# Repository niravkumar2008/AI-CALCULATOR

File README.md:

# AI Calculator

> **Update 2026-10-11:** this README describes the e-paper prototype firmware and simulators in this branch.
> Current state: the product is branded **Proofline**; the **v15 colour-LCD board** is ordered (5 samples, then
> bulk; v14 was never ordered) and its firmware lives on branch `claude/v15-mode4-menu`, where **MODE 4 opens
> Apps** (AI Solve, Type it, History, Notes, Geography, Periodic Table, Settings incl. Link calculator) and exam
> mode turns all apps off. The website, subscription server and store are in `web/` (start with
> [web/SITE_README.md](web/SITE_README.md) and [docs/web/GUIDE.md](docs/web/GUIDE.md)); nothing is deployed.
> The firmware still talks to the older Python server/proxy; connecting it to the new server is the open
> "stage 2" of [docs/web/PLAN.md](docs/web/PLAN.md). (The "Stage 2" and "Stage 4" headings below are the
> firmware's own older stage numbers, not the web plan's.)

## Stage 4: the full calculator

The device now works like a Casio fx-300ES PLUS in COMP mode, with the AI photo solver as mode 4 in the MODE menu. The same C++ code runs in three places:

| Where | How |
| --- | --- |
| **Browser** | `AI_Calc_Simulator.html` (next to the exe; same as `sim/web/simulator.html`): double-click to open in Chrome or Edge. Clickable keypad, test bench (demo replies, hotspot/key switches, clock fast-forward, USB unlock). For real scans, pick Photo or Typed problem and paste your API key: it then sends exactly what the ESP32 sends (upright, grayscale, max 1600 px JPEG, same request, model, streaming and error handling). Direct API calls only work in this local file; the Claude artifact page blocks them. |
| **Windows** | `AI_Calc_Simulator.exe`: type on the keyboard (key list at the bottom of the window). **F6 scans a photo** (needs `api_key.txt` next to the exe). |
| **Tester** | `firmware/`: see [firmware/README.md](firmware/README.md). |

What the calculator does:

- **COMP maths:** + − × ÷, exact fractions (1÷3 = 1⌟3, S⇔D for decimal), powers, roots, x², x³, x⁻¹, x!, nPr, nCr, log (with base), ln, eˣ, 10ˣ, sin/cos/tan and inverses, hyp menu, Abs, %, π, e, Ran#, Rnd, ENG. Casio priorities: implicit × binds tighter than ÷ (1÷2π = 1÷(2π)), (−)2² = −4, brackets close themselves at the end. 10 significant digits, Norm1/Norm2.
- **Editing:** cursor with ◀ ▶ (wraps), DEL, SHIFT DEL = INS (overwrite), ▲ ▼ replay of the last 20 sums, Ans / PreAns, carry on from Ans with an operator.
- **Errors:** Math ERROR / Syntax ERROR / Stack ERROR with [AC] Cancel and [◀][▶] Goto.
- **Memory:** STO / RCL into A–F, X, Y, M; ALPHA types a variable; M+ / M−; SHIFT 9 = CLR (Setup / Memory / All).
- **MODE:** 1 COMP, 2 STAT and 3 TABLE (later), 4 AI SOLVE.
- **SETUP (SHIFT MODE):** 1–3 Deg / Rad / Gra, 4–5 Norm1 / Norm2, 6 Wi-Fi & key, 7 Screen look (Plain / LCD dots), 8 Exam mode.
- **AI SOLVE:** = scans; answer, question and steps scroll with ▲ ▼. If the photo is a calculation, Claude also sends it as `expression` and it is **typed into the main screen** for you to check, edit and press = (AC from the answer takes you there). Unclear scans are flagged on the main screen in reverse video.
- **Exam mode:** SETUP 8 then =, or SHIFT, 7, ON while off. AI, camera and Wi-Fi off; black status bar with a padlock and the time it's been on; survives power-off and restarts. Ends only with the USB cable (`exam off` over serial) or after 12 hours. CLR All doesn't end it.
- **Power:** SHIFT AC = OFF, auto-off after 10 minutes idle.

Screen: 125×61 pixels (the 2.13" e-paper at 2×) = 25 characters × 7 rows; row 0 is the status bar (S, A, M, STO/RCL, D/R/G, Wi-Fi, AI, ▲▼).

New code: `core/calc_engine.*` (tokens, parser, exact fractions, formatting), `core/device.*` (keys, menus, modes, exam, drawing), `sim/web/` (browser build). Tests: 422 checks, `./build/tests`.

Rebuild the browser simulator after changing `core/`: install [Emscripten](https://emscripten.org), then `sim/web/build.sh`.

## Stage 2: Windows simulator (AI flow)

Software for a modified Casio fx-300ES Plus that does one thing: take a picture of a problem and show Claude's answer and the steps to it.

Stage 2 runs the whole flow in a Windows simulator with **real Claude calls**: a photo file stands in for the camera.

## Run it

1. Extract the zip anywhere.
2. Create `api_key.txt` next to `AI_Calc_Simulator.exe` containing your Claude API key (from [console.anthropic.com](https://console.anthropic.com), *API Keys*). One line, nothing else. Setting a monthly spend limit in the Console is a good idea.
3. Double-click `AI_Calc_Simulator.exe`. (Windows may show a SmartScreen warning for an unsigned app: *More info → Run anyway*.)
4. Press Enter and pick a photo of a problem (JPG, PNG, HEIC if Windows can open it).

What happens: the photo is rotated upright, shrunk to at most 1600 px, turned grayscale, and sent to Claude Sonnet 5.5. Claude may think first on harder problems. The answer appears as soon as it arrives, and the steps follow a moment later.

**No `api_key.txt`?** The simulator falls back to Stage 1's sample mode and plays back the hand-written replies in `samples/`. The key file is re-read on every request, so you can add or fix it without restarting.

**Privacy:** the photo is sent only when you press Enter and pick a file. It is kept in memory only. `api_key.txt` is listed in `.gitignore`, so it is never committed to your repo.

| Laptop key | Calculator key | What it does |
| --- | --- | --- |
| Enter or `=` | `=` | Calculate; in AI SOLVE: take a picture / retake / retry |
| Esc | `AC` | Clear, back, or cancel while solving |
| Backspace | `DEL` | Delete |
| Arrows | REPLAY pad | Cursor, history, scroll |
| `m` then `4` | MODE 4 | AI SOLVE |
| Other keys | see `keysForChar` in `core/device.h` | s c t = sin cos tan, `[` SHIFT, `]` ALPHA ... |
| F2 / F3 | — | Simulate hotspot / API key on or off |
| F4 | `ON` / `SHIFT`+`AC` | Power on/off |
| F5 | — | USB cable: ends exam mode |

If Claude isn't sure it read the photo correctly (confidence below 0.8), you see what was unclear first: press `=` to retake, or ↓ to see the answer anyway.

## Messages you might see

| Screen | Meaning |
| --- | --- |
| CLAUDE ERROR / API key was rejected | Check `api_key.txt` |
| CLAUDE BUSY | Rate limit or Claude overloaded; try again shortly |
| NO CONNECTION | No internet, or the connection dropped mid-reply |
| TIMED OUT | No reply within 2 minutes |
| CAMERA ERROR / Couldn't open that image | Windows can't decode that file type |

## What's in here

```
AI_Calc_Simulator.exe   Windows simulator (built from the source below)
samples/                Hand-written example replies in Claude's reply format
core/                   Portable C++17 device logic, shared with the future ESP32 firmware
  device.*              The whole calculator: keys, COMP editing, menus, AI SOLVE, exam mode, status bar
  calc_engine.*         Tokens, Casio-order parser, exact fractions, number formatting, typed-text parser
  app.*                 AI SOLVE screens (Ready, Solving, Warning, Answer, Message)
  claude_api.*          Claude's instructions, reply schema, request body, stream reader, error mapping
  framebuffer.*         125x61 1-bit screen buffer (the e-paper at 2x)
  font*.cpp/h           5x7 font (X11 misc-fixed, public domain) incl. Greek, sub/superscripts
  text.*                Word wrap for 25-character lines
  json.*, solve_result.*  Reading Claude's reply
sim/win32_main.cpp      Simulator: Win32 window, file dialog as camera, WIC photo shrinking, WinHTTP
sim/web/                Browser simulator: web_main.cpp (JS bridge), page.html, build.sh -> simulator.html
tests/                  Unit tests + screen snapshots (tests/golden)
tools/gen_font.py       Regenerates core/font_data.cpp
firmware/               ESP32-S3 tester firmware (PlatformIO), Stage 4
```

## Reply format

Claude replies with exactly this JSON, enforced by the API's structured output. The field order is fixed, so the answer streams in before the steps:

```json
{
  "readable": true,
  "confidence": 0.95,
  "unclear": ["line 1: '7' could be '1'"],
  "expression": "sqrt(2*9.81*5.0)",
  "answer": "v ≈ 9.90 m/s",
  "read_as": "the question as understood",
  "steps": ["step 1", "step 2"]
}
```

The instructions (in `core/claude_api.cpp`) tell Claude the screen is 25×6 characters, so the answer is kept to about 2 lines, steps to about 75 characters, in calculator notation with no LaTeX. `expression` is the calculation in typed form (`*`, `/`, `^`, `sqrt(`, `pi`, `E` for ×10ˣ), or empty for word problems.

## Build from source (optional)

The tests run on Linux or macOS: `cmake -S . -B build && cmake --build build && ./build/tests` (run from this folder).
The exe is cross-compiled with MinGW:
`x86_64-w64-mingw32-g++ -std=c++17 -O2 -static -mwindows -o AI_Calc_Simulator.exe sim/win32_main.cpp core/*.cpp -lgdi32 -lwinhttp -lwindowscodecs -lole32 -loleaut32 -lcomdlg32`

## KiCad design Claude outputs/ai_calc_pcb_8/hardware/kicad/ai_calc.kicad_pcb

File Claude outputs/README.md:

# AI Calculator

## Stage 4: the full calculator

The device now works like a Casio fx-300ES PLUS in COMP mode, with the AI photo solver as mode 4 in the MODE menu. The same C++ code runs in three places:

| Where | How |
| --- | --- |
| **Browser** | `sim/web/simulator.html`: double-click to open. Clickable keypad, test bench (demo replies, hotspot/key switches, clock fast-forward, USB unlock). For real scans, pick Photo or Typed problem and paste your API key: it then sends exactly what the ESP32 sends (upright, grayscale, max 1600 px JPEG, same request, model, streaming and error handling). Direct API calls only work in this local file; the Claude artifact page blocks them. |
| **Windows** | `AI_Calc_Simulator.exe`: type on the keyboard (key list at the bottom of the window). |
| **Tester** | `firmware/`: see [firmware/README.md](firmware/README.md). |

What the calculator does:

- **COMP maths:** + − × ÷, exact fractions (1÷3 = 1⌟3, S⇔D for decimal), powers, roots, x², x³, x⁻¹, x!, nPr, nCr, log (with base), ln, eˣ, 10ˣ, sin/cos/tan and inverses, hyp menu, Abs, %, π, e, Ran#, Rnd, ENG. Casio priorities: implicit × binds tighter than ÷ (1÷2π = 1÷(2π)), (−)2² = −4, brackets close themselves at the end. 10 significant digits, Norm1/Norm2.
- **Editing:** cursor with ◀ ▶ (wraps), DEL, SHIFT DEL = INS (overwrite), ▲ ▼ replay of the last 20 sums, Ans / PreAns, carry on from Ans with an operator.
- **Errors:** Math ERROR / Syntax ERROR / Stack ERROR with [AC] Cancel and [◀][▶] Goto.
- **Memory:** STO / RCL into A–F, X, Y, M; ALPHA types a variable; M+ / M−; SHIFT 9 = CLR (Setup / Memory / All).
- **MODE:** 1 COMP, 2 STAT and 3 TABLE (later), 4 AI SOLVE.
- **SETUP (SHIFT MODE):** 1–3 Deg / Rad / Gra, 4–5 Norm1 / Norm2, 6 Wi-Fi & key, 7 Screen look (Plain / LCD dots), 8 Exam mode.
- **AI SOLVE:** = scans; answer, question and steps scroll with ▲ ▼. If the photo is a calculation, Claude also sends it as `expression` and it is **typed into the main screen** for you to check, edit and press = (AC from the answer takes you there). Unclear scans are flagged on the main screen in reverse video.
- **Exam mode:** SETUP 8 then =, or SHIFT, 7, ON while off. AI, camera and Wi-Fi off; black status bar with a padlock and the time it's been on; survives power-off and restarts. Ends only with the USB cable (`exam off` over serial) or after 12 hours. CLR All doesn't end it.
- **Power:** SHIFT AC = OFF, auto-off after 10 minutes idle.

Screen: 125×61 pixels (the 2.13" e-paper at 2×) = 25 characters × 7 rows; row 0 is the status bar (S, A, M, STO/RCL, D/R/G, Wi-Fi, AI, ▲▼).

New code: `core/calc_engine.*` (tokens, parser, exact fractions, formatting), `core/device.*` (keys, menus, modes, exam, drawing), `sim/web/` (browser build). Tests: 422 checks, `./build/tests`.

Rebuild the browser simulator after changing `core/`: install [Emscripten](https://emscripten.org), then `sim/web/build.sh`.

## Stage 2: Windows simulator (AI flow)

Software for a modified Casio fx-300ES Plus that does one thing: take a picture of a problem and show Claude's answer and the steps to it.

Stage 2 runs the whole flow in a Windows simulator with **real Claude calls**: a photo file stands in for the camera.

## Run it

1. Extract the zip anywhere.
2. Create `api_key.txt` next to `AI_Calc_Simulator.exe` containing your Claude API key (from [console.anthropic.com](https://console.anthropic.com), *API Keys*). One line, nothing else. Setting a monthly spend limit in the Console is a good idea.
3. Double-click `AI_Calc_Simulator.exe`. (Windows may show a SmartScreen warning for an unsigned app: *More info → Run anyway*.)
4. Press Enter and pick a photo of a problem (JPG, PNG, HEIC if Windows can open it).

What happens: the photo is rotated upright, shrunk to at most 1600 px, turned grayscale, and sent to Claude Sonnet 5.5. Claude may think first on harder problems. The answer appears as soon as it arrives, and the steps follow a moment later.

**No `api_key.txt`?** The simulator falls back to Stage 1's sample mode and plays back the hand-written replies in `samples/`. The key file is re-read on every request, so you can add or fix it without restarting.

**Privacy:** the photo is sent only when you press Enter and pick a file. It is kept in memory only. `api_key.txt` is listed in `.gitignore`, so it is never committed to your repo.

| Laptop key | Calculator key | What it does |
| --- | --- | --- |
| Enter or `=` | `=` | Calculate; in AI SOLVE: take a picture / retake / retry |
| Esc | `AC` | Clear, back, or cancel while solving |
| Backspace | `DEL` | Delete |
| Arrows | REPLAY pad | Cursor, history, scroll |
| `m` then `4` | MODE 4 | AI SOLVE |
| Other keys | see `keysForChar` in `core/device.h` | s c t = sin cos tan, `[` SHIFT, `]` ALPHA ... |
| F2 / F3 | — | Simulate hotspot / API key on or off |
| F4 | `ON` / `SHIFT`+`AC` | Power on/off |
| F5 | — | USB cable: ends exam mode |

If Claude isn't sure it read the photo correctly (confidence below 0.8), you see what was unclear first: press `=` to retake, or ↓ to see the answer anyway.

## Messages you might see

| Screen | Meaning |
| --- | --- |
| CLAUDE ERROR / API key was rejected | Check `api_key.txt` |
| CLAUDE BUSY | Rate limit or Claude overloaded; try again shortly |
| NO CONNECTION | No internet, or the connection dropped mid-reply |
| TIMED OUT | No reply within 2 minutes |
| CAMERA ERROR / Couldn't open that image | Windows can't decode that file type |

## What's in here

```
AI_Calc_Simulator.exe   Windows simulator (built from the source below)
samples/                Hand-written example replies in Claude's reply format
core/                   Portable C++17 device logic, shared with the future ESP32 firmware
  device.*              The whole calculator: keys, COMP editing, menus, AI SOLVE, exam mode, status bar
  calc_engine.*         Tokens, Casio-order parser, exact fractions, number formatting, typed-text parser
  app.*                 AI SOLVE screens (Ready, Solving, Warning, Answer, Message)
  claude_api.*          Claude's instructions, reply schema, request body, stream reader, error mapping
  framebuffer.*         125x61 1-bit screen buffer (the e-paper at 2x)
  font*.cpp/h           5x7 font (X11 misc-fixed, public domain) incl. Greek, sub/superscripts
  text.*                Word wrap for 25-character lines
  json.*, solve_result.*  Reading Claude's reply
sim/win32_main.cpp      Simulator: Win32 window, file dialog as camera, WIC photo shrinking, WinHTTP
sim/web/                Browser simulator: web_main.cpp (JS bridge), page.html, build.sh -> simulator.html
tests/                  Unit tests + screen snapshots (tests/golden)
tools/gen_font.py       Regenerates core/font_data.cpp
firmware/               ESP32-S3 tester firmware (PlatformIO), Stage 4
```

## Reply format

Claude replies with exactly this JSON, enforced by the API's structured output. The field order is fixed, so the answer streams in before the steps:

```json
{
  "readable": true,
  "confidence": 0.95,
  "unclear": ["line 1: '7' could be '1'"],
  "expression": "sqrt(2*9.81*5.0)",
  "answer": "v ≈ 9.90 m/s",
  "read_as": "the question as understood",
  "steps": ["step 1", "step 2"]
}
```

The instructions (in `core/claude_api.cpp`) tell Claude the screen is 25×6 characters, so the answer is kept to about 2 lines, steps to about 75 characters, in calculator notation with no LaTeX. `expression` is the calculation in typed form (`*`, `/`, `^`, `sqrt(`, `pi`, `E` for ×10ˣ), or empty for word problems.

## Build from source (optional)

The tests run on Linux or macOS: `cmake -S . -B build && cmake --build build && ./build/tests` (run from this folder).
The exe is cross-compiled with MinGW:
`x86_64-w64-mingw32-g++ -std=c++17 -O2 -static -mwindows -o AI_Calc_Simulator.exe sim/win32_main.cpp core/*.cpp -lgdi32 -lwinhttp -lwindowscodecs -lole32 -loleaut32 -lcomdlg32`

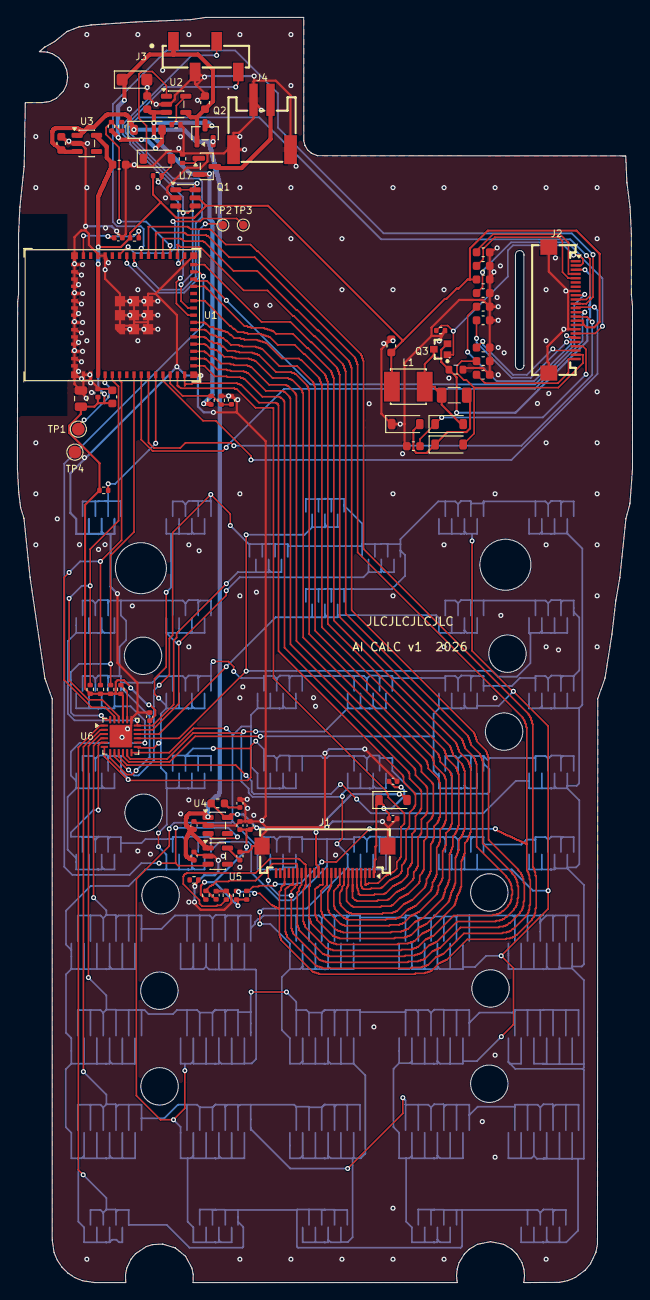
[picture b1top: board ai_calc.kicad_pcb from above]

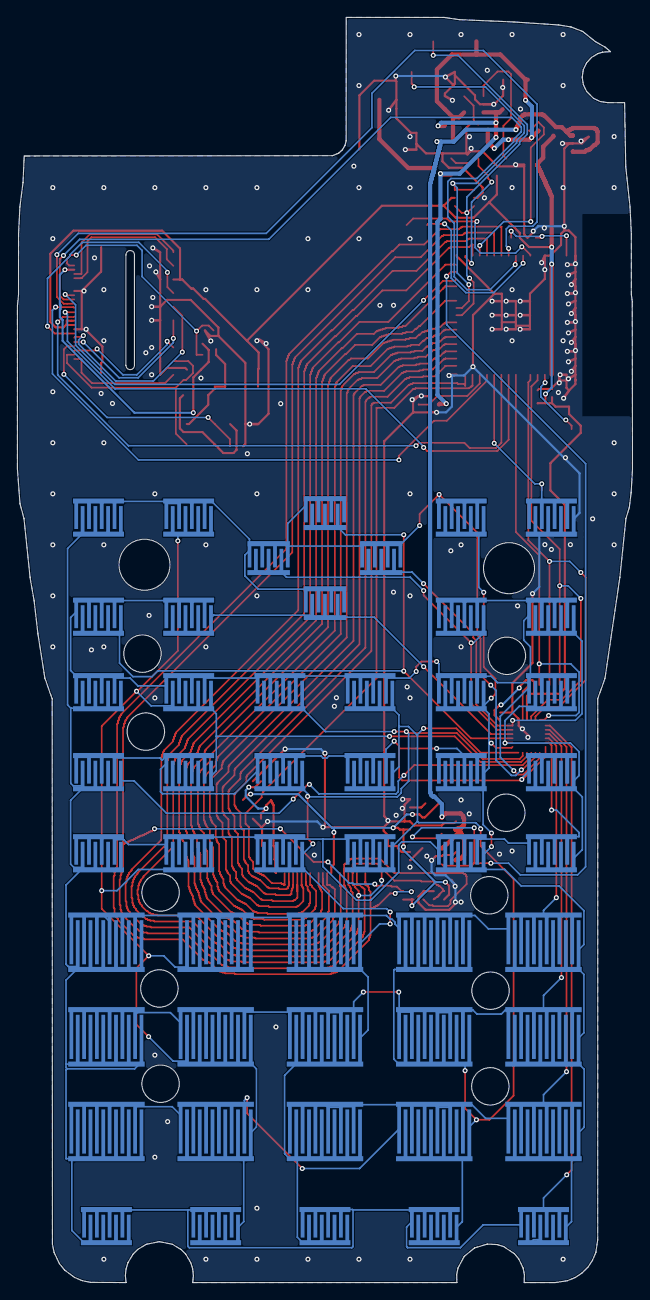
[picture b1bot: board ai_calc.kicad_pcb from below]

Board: 2 copper layers, 72.3 x 148.8 mm, 140 parts (50 on the bottom side), 81 nets.

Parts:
C1: 22uF; C_0805_2012Metric
C2, C9, C12, C17, C18, C31: 100nF; C_0402_1005Metric
C3, C8: 10uF; C_0603_1608Metric
C4, C10, C14: 1uF; C_0402_1005Metric
C5, C6, C7, C19: 4.7uF; C_0603_1608Metric
C11, C13, C15, C16: 2.2uF; C_0402_1005Metric
C20: 4.7uF 50V; C_1206_3216Metric
C21, C22, C23, C24, C25, C26, C27, C28, C29, C30: 1uF 50V; C_0603_1608Metric
D1, D2, D3, D4, D5: B5819W; D_SOD-123
D6: B5819W (STAT level clamp); D_SOD-123
D7: SMF5.0A (VBUS TVS); D_SMF
FB1: 600R@100MHz; L_0603_1608Metric
H1, H3: Screw boss hole 6.0 (Casio post); ScrewBoss_Hole_6.0mm
H2, H4, H5, H6, H7, H8, H9, H10, H11, H12: Post hole 4.4 (Casio peg); Post_Hole_4.4mm
J1: Camera FPC 24P 0.5mm dual-contact (OV5640, cable 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; FPC_24P_P0.5mm_DualContact_C6364666_CamReversed
J2: E-paper FPC 24P 0.5mm dual-contact (2.13in V4); FPC_24P_P0.5mm_DualContact_C6364666
J3: Magnetic USB (Adafruit 5358): VBUS GND D- D+; PinSocket_1x04_P2.54mm_SMD_H5.0_C42379197
J4: Battery JST-PH (Adafruit 1570); JST_PH_S2B-PH-SM4-TB_LCSC
L1: 68uH SMNR4020; L_SMNR4020_4.0x4.0mm
Q1: AO3401A (reverse battery); SOT-23
Q2: AO3401A (load share); SOT-23
Q3: SI1308EDL-T1-GE3; SOT-323_SI1308EDL
R1, R4, R8, R9, R11, R15, R16: 10k; R_0402_1005Metric
R2: 20k (50 mA); R_0402_1005Metric
R3, R10, R17, R20: 100k; R_0402_1005Metric
R5: 20k; R_0402_1005Metric
R6, R7: 1M; R_0402_1005Metric
R12: 3R (2.13in B/W panel); R_0603_1608Metric
R13, R14, R18, R19: 4.7k; R_0402_1005Metric
SW1: SHIFT; KeyPad_6.0x4.5
SW2: ALPHA; KeyPad_6.0x4.5
SW3: MODE; KeyPad_6.0x4.5
SW4: Abs; KeyPad_6.0x4.5
SW5: x^3; KeyPad_6.0x4.5
SW6: x^-1; KeyPad_6.0x4.5
SW7: log_a; KeyPad_6.0x4.5
SW8: a/b; KeyPad_6.0x4.5
SW9: sqrt; KeyPad_6.0x4.5
SW10: x^2; KeyPad_6.0x4.5
SW11: x^n; KeyPad_6.0x4.5
SW12: log; KeyPad_6.0x4.5
SW13: ln; KeyPad_6.0x4.5
SW14: (-); KeyPad_6.0x4.5
SW15: deg-min-sec; KeyPad_6.0x4.5
SW16: hyp; KeyPad_6.0x4.5
SW17: sin; KeyPad_6.0x4.5
SW18: cos; KeyPad_6.0x4.5
SW19: tan; KeyPad_6.0x4.5
SW20: RCL; KeyPad_6.0x4.5
SW21: ENG; KeyPad_6.0x4.5
SW22: (; KeyPad_6.0x4.5
SW23: ); KeyPad_6.0x4.5
SW24: S<>D; KeyPad_6.0x4.5
SW25: M+; KeyPad_6.0x4.5
SW26: 7; KeyPad_9.0x7.0
SW27: 8; KeyPad_9.0x7.0
SW28: 9; KeyPad_9.0x7.0
SW29: DEL; KeyPad_9.0x7.0
SW30: AC; KeyPad_9.0x7.0
SW31: 4; KeyPad_9.0x7.0
SW32: 5; KeyPad_9.0x7.0
SW33: 6; KeyPad_9.0x7.0
SW34: x; KeyPad_9.0x7.0
SW35: /; KeyPad_9.0x7.0
SW36: 1; KeyPad_9.0x7.0
SW37: 2; KeyPad_9.0x7.0
SW38: 3; KeyPad_9.0x7.0
SW39: +; KeyPad_9.0x7.0
SW40: -; KeyPad_9.0x7.0
SW41: 0; KeyPad_6.0x4.5
SW42: .; KeyPad_6.0x4.5
SW43: x10^x; KeyPad_6.0x4.5
SW44: Ans; KeyPad_6.0x4.5
SW45: =; KeyPad_6.0x4.5
SW46: UP; KeyPad_5.0x4.0
SW47: DOWN; KeyPad_5.0x4.0
SW48: LEFT; KeyPad_5.0x4.0
SW49: RIGHT; KeyPad_5.0x4.0
SW50: ON; KeyPad_6.0x4.5
TP1: BOOT; TestPoint_Pad_D1.5mm
TP2: UART_TX; TestPoint_Pad_D1.0mm
TP3: UART_RX; TestPoint_Pad_D1.0mm
TP4: GND; TestPoint_Pad_D1.5mm
U1: ESP32-S3-MINI-1-N4R2; ESP32-S3-MINI-1
U2: MCP73831T-2ACI/OT; SOT-23-5
U3: AP2112K-3.3TRG1; SOT-23-5
U4: ME6211C28M5G-N; SOT-23-5
U5: ME6211C15M5G-N; SOT-23-5
U6: TCA8418RTWR; HVQFN-24-1EP_4x4mm_P0.5mm_EP2.6x2.6mm
U7: USBLC6-2SC6; SOT-23-6

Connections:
+3V3: C1.1, C2.1, C3.1, C8.1, C19.1, C23.1, C31.1, J2.15, J2.16, L1.1, R1.1, R13.1, R14.1, R15.1, R16.1, R17.1, R20.1, U1.3, U3.5, U6.21, U7.5
/Keypad and TCA8418/COL0: SW1.2, SW8.2, SW14.2, SW20.2, SW26.2, SW31.2, SW36.2, SW41.2, U6.9
/Keypad and TCA8418/COL1: SW2.2, SW9.2, SW15.2, SW21.2, SW27.2, SW32.2, SW37.2, SW42.2, U6.10
/Keypad and TCA8418/COL2: SW10.2, SW16.2, SW22.2, SW28.2, SW33.2, SW38.2, SW43.2, U6.11
/Keypad and TCA8418/COL3: SW11.2, SW17.2, SW23.2, SW29.2, SW34.2, SW39.2, SW44.2, U6.12
/Keypad and TCA8418/COL4: SW3.2, SW12.2, SW18.2, SW24.2, SW30.2, SW35.2, SW40.2, SW45.2, U6.13
/Keypad and TCA8418/COL5: SW13.2, SW19.2, SW25.2, U6.14
/Keypad and TCA8418/COL6: SW4.2, SW46.2, U6.15
/Keypad and TCA8418/COL7: SW5.2, SW47.2, U6.16
/Keypad and TCA8418/COL8: SW6.2, SW48.2, U6.17
/Keypad and TCA8418/COL9: SW7.2, SW49.2, U6.18
/Keypad and TCA8418/ROW0: SW1.1, SW2.1, SW3.1, SW46.1, SW47.1, SW48.1, SW49.1, U6.8
/Keypad and TCA8418/ROW1: SW4.1, SW5.1, SW6.1, SW7.1, SW8.1, SW9.1, SW10.1, SW11.1, SW12.1, SW13.1, U6.7
/Keypad and TCA8418/ROW2: SW14.1, SW15.1, SW16.1, SW17.1, SW18.1, SW19.1, U6.6
/Keypad and TCA8418/ROW3: SW20.1, SW21.1, SW22.1, SW23.1, SW24.1, SW25.1, U6.5
/Keypad and TCA8418/ROW4: SW26.1, SW27.1, SW28.1, SW29.1, SW30.1, U6.4
/Keypad and TCA8418/ROW5: SW31.1, SW32.1, SW33.1, SW34.1, SW35.1, U6.3
/Keypad and TCA8418/ROW6: SW36.1, SW37.1, SW38.1, SW39.1, SW40.1, U6.2
/Keypad and TCA8418/ROW7: SW41.1, SW42.1, SW43.1, SW44.1, SW45.1, U6.1
BAT+: J4.2, Q1.3
BOOT: TP1.1, U1.4
CAM_2V8: C11.1, C12.1, D2.2, FB1.1, J1.11, R8.1, R18.1, R19.1, U4.5
CAM_AF: C16.1, C17.1, D2.1, J1.24
CAM_AVDD: C13.1, FB1.2, J1.4
CAM_D0: J1.19, U1.17
CAM_D1: J1.21, U1.15
CAM_D2: J1.22, U1.14
CAM_D3: J1.20, U1.16
CAM_D4: J1.18, U1.18
CAM_D5: J1.16, U1.20
CAM_D6: J1.14, U1.21
CAM_D7: J1.12, U1.25
CAM_DVDD: C15.1, J1.10, U5.5
CAM_HREF: J1.9, U1.27
CAM_PCLK: J1.17, U1.19
CAM_PWDN: J1.8, R9.1, U1.30
CAM_PWR_EN: R10.1, U1.29, U4.3, U5.3
CAM_RESET: C18.1, J1.6, R8.2, U1.34
CAM_SIOC: J1.5, R19.2, U1.35
CAM_SIOD: J1.3, R18.2, U1.36
CAM_VSYNC: J1.7, U1.32
CAM_XCLK: J1.13, U1.22
CHG_PROG: R2.1, U2.5
CHG_STAT: D6.2, R20.2, U1.31
CHG_STAT_RAW: D6.1, U2.1
EN: C4.1, R1.2, U1.45
EPD_BUSY: J2.9, U1.28
EPD_CLK: J2.13, U1.9
EPD_CS: J2.12, U1.12
EPD_DC: J2.11, U1.37
EPD_DIN: J2.14, U1.10
EPD_GDR: J2.2, Q3.1, R11.1
EPD_PREVGH: C27.1, D3.1, J2.21
EPD_PREVGL: C29.1, D5.2, J2.23
EPD_PUMP: C20.2, D4.2, D5.1
EPD_RESE: J2.3, Q3.2, R12.1
EPD_RST: J2.10, U1.38
EPD_SW: C20.1, D3.2, L1.2, Q3.3
EPD_VCOM: C30.1, J2.24
EPD_VDD: C24.1, J2.18
EPD_VGH: C22.1, J2.5
EPD_VGL: C21.1, J2.4
EPD_VPP: C25.1, J2.19
EPD_VSH: C26.1, J2.20
EPD_VSL: C28.1, J2.22
GND: C1.2, C2.2, C3.2, C4.2, C5.2, C6.2, C7.2, C8.2, C9.2, C10.2, C11.2, C12.2, C13.2, C14.2, C15.2, C16.2, C17.2, C18.2, C19.2, C21.2, C22.2, C23.2, C24.2, C25.2, C26.2, C27.2, C28.2, C29.2, C30.2, C31.2, D4.1, D7.2, J1.2, J1.15, J1.23, J1.MP, J2.8, J2.17, J2.MP, J3.2, J4.1, J4.MP, R2.2, R3.2, R5.2, R7.2, R9.2, R10.2, R11.2, R12.2, SW50.2, TP4.1, U1.1, U1.2, U1.42, U1.43, U1.46, U1.47, U1.48, U1.49, U1.50, U1.51, U1.52, U1.53, U1.54, U1.55, U1.56, U1.57, U1.58, U1.59, U1.60, U1.61, U1.62, U1.63, U1.64, U1.65, U2.2, U3.2, U4.2, U5.2, U6.19, U6.25, U7.2
I2C_SCL: R14.2, U1.6, U6.23
I2C_SDA: R13.2, U1.5, U6.22
KEYPAD_INT: R15.2, U1.8, U6.24
KEY_ON: R17.2, SW50.1, U1.11
Q1_G: Q1.1, R3.1
SYS: C7.1, C10.1, C14.1, D1.1, Q2.2, U3.1, U3.3, U4.1, U5.1
TCA_RESET: R16.2, U6.20
UART_RX: TP3.1, U1.40
UART_TX: TP2.1, U1.39
USB_DM: J3.3, U1.23, U7.3, U7.4
USB_DP: J3.4, U1.24, U7.1, U7.6
VBAT_P: C6.1, Q1.2, Q2.3, R6.1, U2.3
VBAT_SENSE: C9.1, R6.2, R7.1, U1.13
VBUS: C5.1, D1.2, D7.1, J3.1, Q2.1, R4.1, U2.4
VBUS_SENSE: R4.2, R5.1, U1.33

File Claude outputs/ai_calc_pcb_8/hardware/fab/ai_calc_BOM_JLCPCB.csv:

"Comment","Designator","Footprint","LCSC Part #"
"22uF","C1","Capacitor_SMD:C_0805_2012Metric","C45783"
"100nF","C2,C9,C12,C17,C18,C31","Capacitor_SMD:C_0402_1005Metric","C1525"
"10uF","C3,C8","Capacitor_SMD:C_0603_1608Metric","C19702"
"1uF","C4,C10,C14","Capacitor_SMD:C_0402_1005Metric","C52923"
"4.7uF","C5-C7,C19","Capacitor_SMD:C_0603_1608Metric","C19666"
"2.2uF","C11,C13,C15,C16","Capacitor_SMD:C_0402_1005Metric","C12530"
"4.7uF 50V","C20","Capacitor_SMD:C_1206_3216Metric","C29823"
"1uF 50V","C21-C30","Capacitor_SMD:C_0603_1608Metric","C15849"
"B5819W","D1-D5","Diode_SMD:D_SOD-123","C8598"
"B5819W (STAT level clamp)","D6","Diode_SMD:D_SOD-123","C8598"
"SMF5.0A (VBUS TVS)","D7","Diode_SMD:D_SMF","C193402"
"600R@100MHz","FB1","Inductor_SMD:L_0603_1608Metric","C1002"
"Camera FPC 24P 0.5mm dual-contact (OV5640, cable contacts down)","J1","ai_calc:FPC_24P_P0.5mm_DualContact_C6364666_CamReversed","C6364666"
"E-paper FPC 24P 0.5mm dual-contact (2.13in V4)","J2","ai_calc:FPC_24P_P0.5mm_DualContact_C6364666","C6364666"
"Magnetic USB (Adafruit 5358): VBUS GND D- D+","J3","ai_calc:PinSocket_1x04_P2.54mm_SMD_H5.0_C42379197","C42379197"
"Battery JST-PH (Adafruit 1570)","J4","ai_calc:JST_PH_S2B-PH-SM4-TB_LCSC","C295747"
"68uH SMNR4020","L1","ai_calc:L_SMNR4020_4.0x4.0mm","C135265"
"AO3401A (reverse battery)","Q1","Package_TO_SOT_SMD:SOT-23","C15127"
"AO3401A (load share)","Q2","Package_TO_SOT_SMD:SOT-23","C15127"
"SI1308EDL-T1-GE3","Q3","ai_calc:SOT-323_SI1308EDL","C469327"
"10k","R1,R4,R8,R9,R11,R15,R16","Resistor_SMD:R_0402_1005Metric","C25744"
"20k (50 mA)","R2","Resistor_SMD:R_0402_1005Metric","C25765"
"100k","R3,R10,R17,R20","Resistor_SMD:R_0402_1005Metric","C25741"
"20k","R5","Resistor_SMD:R_0402_1005Metric","C25765"
"1M","R6,R7","Resistor_SMD:R_0402_1005Metric","C26083"
"3R (2.13in B/W panel)","R12","Resistor_SMD:R_0603_1608Metric","C23157"
"4.7k","R13,R14,R18,R19","Resistor_SMD:R_0402_1005Metric","C25900"
"ESP32-S3-MINI-1-N4R2","U1","ai_calc:ESP32-S3-MINI-1","C3013941"
"MCP73831T-2ACI/OT","U2","Package_TO_SOT_SMD:SOT-23-5","C424093"
"AP2112K-3.3TRG1","U3","Package_TO_SOT_SMD:SOT-23-5","C51118"
"ME6211C28M5G-N","U4","Package_TO_SOT_SMD:SOT-23-5","C53099"
"ME6211C15M5G-N","U5","Package_TO_SOT_SMD:SOT-23-5","C53100"
"TCA8418RTWR","U6","Package_DFN_QFN:HVQFN-24-1EP_4x4mm_P0.5mm_EP2.6x2.6mm","C138713"
"USBLC6-2SC6","U7","Package_TO_SOT_SMD:SOT-23-6","C7519"

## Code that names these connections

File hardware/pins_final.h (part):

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// ---- Camera: OV5640 autofocus, 24-pin 0.5 mm FPC socket J1 (esp32-camera naming: D0..D7 = Y2..Y9)
// Stage 6 (2026-10-02): pins re-ordered so the bus leaves the module in the same order as the
// socket pins (no crossings, 0.6 mm track pitch). Same set of GPIOs as before, different roles.
constexpr int PIN_CAM_XCLK  = 18;  // [CAM_XCLK] 20 MHz clock out (LEDC)
constexpr int PIN_CAM_SIOD  = 40;  // [CAM_SIOD] SCCB data, own bus (not shared with the keypad); MTDO (JTAG) pin
constexpr int PIN_CAM_SIOC  = 39;  // [CAM_SIOC] SCCB clock; MTCK (JTAG) pin. 4.7 k pull-ups R18/R19 go to CAM_2V8
constexpr int PIN_CAM_D0    = 13;  // [CAM_D0] Y2
constexpr int PIN_CAM_D1    = 11;  // [CAM_D1] Y3
constexpr int PIN_CAM_D2    = 10;  // [CAM_D2] Y4
constexpr int PIN_CAM_D3    = 12;  // [CAM_D3] Y5
constexpr int PIN_CAM_D4    = 14;  // [CAM_D4] Y6
constexpr int PIN_CAM_D5    = 16;  // [CAM_D5] Y7
constexpr int PIN_CAM_D6    = 17;  // [CAM_D6] Y8
constexpr int PIN_CAM_D7    = 21;  // [CAM_D7] Y9
constexpr int PIN_CAM_VSYNC = 36;  // [CAM_VSYNC]
constexpr int PIN_CAM_HREF  = 47;  // [CAM_HREF]
constexpr int PIN_CAM_PCLK  = 15;  // [CAM_PCLK]
constexpr int PIN_CAM_PWDN  = 48;  // [CAM_PWDN] high = sensor powered down (active high); 10 k pull-down.
                                   // Never drive it high while CAM_2V8 is off (~330 uA into the unpowered sensor).
constexpr int PIN_CAM_RESET = 38;  // [CAM_RESET] low = reset (active low); 10 k pull-up to CAM_2V8 + 100 nF
constexpr int PIN_CAM_PWR_EN = 34; // [CAM_PWR_EN] high = 2.8 V + 1.5 V camera regulators on; R10 100 k pull-down = off in sleep

// ---- E-paper: 2.13" 250x122 bare panel (SSD1680), 24-pin 0.5 mm FPC socket J2 + booster on the board (SPI, write-only)
constexpr int PIN_EPD_CLK  = 5;    // [EPD_CLK]
constexpr int PIN_EPD_DIN  = 6;    // [EPD_DIN] (MOSI)
constexpr int PIN_EPD_CS   = 8;    // [EPD_CS]
constexpr int PIN_EPD_DC   = 41;   // [EPD_DC]
constexpr int PIN_EPD_RST  = 42;   // [EPD_RST]
constexpr int PIN_EPD_BUSY = 33;   // [EPD_BUSY] input; high while the panel is refreshing

// ---- Keypad: 49 keys as an 8 x 10 matrix on a TCA8418 (U6, I2C 0x34); ON has its own pin
constexpr int PIN_I2C_SDA    = 1;  // [I2C_SDA] 4.7 k pull-ups to 3.3 V on the board
constexpr int PIN_I2C_SCL    = 2;  // [I2C_SCL]
constexpr int PIN_KEYPAD_INT = 4;  // [KEYPAD_INT] TCA8418 INT (open drain, 10 k pull-up R15, low while a key event
                                   // waits); RTC pin: wakes the chip from deep sleep (EXT1). Clear it before sleeping
                                   // or R15 draws 330 uA all night.
constexpr int PIN_KEY_ON     = 7;  // [KEY_ON] ON pad to GND, R17 100 k pull-up (board/BOM: 100k C25741); RTC pin: wakes the chip from deep sleep (EXT1, low)
constexpr uint8_t TCA8418_I2C_ADDR = 0x34;
// TCA8418 ~RESET [TCA_RESET] has only a 10 k pull-up (R16): it is NOT wired to the ESP32. The firmware
// re-writes every TCA8418 register at start instead of resetting it.
constexpr int PIN_TCA_RESET  = -1;

// ---- Power
constexpr int PIN_VBAT_SENSE = 9;  // [VBAT_SENSE] ADC1_CH8: battery through 1 M / 1 M (+100 nF), reads half the voltage
constexpr int PIN_VBUS_SENSE = 37; // [VBUS_SENSE] high while a cable is on the magnetic connector (10 k / 20 k from VBUS = 3.3 V
                                   // at 5 V). Not an RTC pin: a cable cannot wake deep sleep
constexpr int PIN_CHG_STAT   = 35; // [CHG_STAT] MCP73831 STAT via Schottky D6, pull-up R20 100 k to VBUS_SENSE (stage 11, review S1):
                                   // low = charging, high = done. With no cable R20 has no supply, so the pin reads low:
                                   // only trust it while VBUS_SENSE is high. No internal pull-up/-down (it would back-feed).
constexpr int PIN_BATTERY    = PIN_VBAT_SENSE;  // old name, kept for older notes

// ---- USB (native USB-Serial-JTAG on the magnetic connector): IO19 = D-, IO20 = D+. Fixed by the chip.
constexpr int PIN_USB_DM = 19;     // [USB_DM]
constexpr int PIN_USB_DP = 20;     // [USB_DP]

// ---- Test pads only: IO0 = BOOT (TP1), IO43/IO44 = UART0 TX/RX (TP2/TP3, debug log), EN = TP7, GND = TP4.
//      Unused: IO3, IO45, IO46 (straps, leave unconnected).
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//      NEVER burn the security / USB-disable eFuses (DIS_USB_SERIAL_JTAG, DIS_DOWNLOAD_MODE,
//      ENABLE_SECURITY_DOWNLOAD, secure boot, flash encryption): they are the only way to lock this board out.
constexpr int PIN_BOOT     = 0;
constexpr int PIN_UART_TX  = 43;
constexpr int PIN_UART_RX  = 44;

// ---- Magnetic connector (Adafruit 5358 / MG04254FRA1S1N, 4 pins at 2.50 mm), J3 pin 1 = the piece's "N" end
// (silk "N" and "+" beside pin 1, "-" beside pin 4). Stage 14 order, set by the Adafruit #5412 cable
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};

constexpr CameraPins kCameraVariants[] = {
    {"Final board (OV5640 AF)", PIN_CAM_PWDN, PIN_CAM_RESET, PIN_CAM_XCLK, PIN_CAM_SIOD, PIN_CAM_SIOC,
     PIN_CAM_D0, PIN_CAM_D1, PIN_CAM_D2, PIN_CAM_D3, PIN_CAM_D4, PIN_CAM_D5, PIN_CAM_D6, PIN_CAM_D7,
     PIN_CAM_VSYNC, PIN_CAM_HREF, PIN_CAM_PCLK},
};

// Every camera GPIO, for powering the camera down: each must end up disabled with no pull
// (a pull or a driven pin back-powers the sensor through its ESD diodes / R18 / R19).
constexpr int kCameraGpios[] = {PIN_CAM_XCLK, PIN_CAM_SIOD,  PIN_CAM_SIOC, PIN_CAM_D0,   PIN_CAM_D1,   PIN_CAM_D2,
                                PIN_CAM_D3,   PIN_CAM_D4,    PIN_CAM_D5,   PIN_CAM_D6,   PIN_CAM_D7,   PIN_CAM_VSYNC,
                                PIN_CAM_HREF, PIN_CAM_PCLK,  PIN_CAM_PWDN, PIN_CAM_RESET};

// ---- Compile-time checks: a typo here fails the build instead of a board.
namespace pins_check {
constexpr int kAll[] = {PIN_CAM_XCLK, PIN_CAM_SIOD, PIN_CAM_SIOC, PIN_CAM_D0, PIN_CAM_D1, PIN_CAM_D2, PIN_CAM_D3,
                        PIN_CAM_D4, PIN_CAM_D5, PIN_CAM_D6, PIN_CAM_D7, PIN_CAM_VSYNC, PIN_CAM_HREF, PIN_CAM_PCLK,
                        PIN_CAM_PWDN, PIN_CAM_RESET, PIN_CAM_PWR_EN, PIN_EPD_CLK, PIN_EPD_DIN, PIN_EPD_CS,
                        PIN_EPD_DC, PIN_EPD_RST, PIN_EPD_BUSY, PIN_I2C_SDA, PIN_I2C_SCL, PIN_KEYPAD_INT,
                        PIN_KEY_ON, PIN_VBAT_SENSE, PIN_VBUS_SENSE, PIN_CHG_STAT, PIN_USB_DM, PIN_USB_DP,
                        PIN_BOOT, PIN_UART_TX, PIN_UART_RX};
constexpr int kCount = sizeof(kAll) / sizeof(kAll[0]);
constexpr bool unique() {
  for (int i = 0; i < kCount; ++i)
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}
static_assert(unique(), "pins_final.h: two signals share one GPIO");
static_assert(legal(), "pins_final.h: a pin is not usable on the ESP32-S3-MINI-1-N4R2");
static_assert(PIN_KEY_ON <= 21 && PIN_KEYPAD_INT <= 21, "deep-sleep wake pins must be RTC GPIOs (IO0..IO21)");
static_assert(PIN_VBAT_SENSE >= 1 && PIN_VBAT_SENSE <= 10, "battery sense must be on ADC1 (IO1..IO10) to work with Wi-Fi");
}  // namespace pins_check

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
